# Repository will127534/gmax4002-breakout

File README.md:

# GMAX4002 breakout board
A basic minimum GMAX4002 (1/1.7" 2048x1200 Global shutter) breakout board for Raspberry Pi

In general this is a simple breakout board for GMAX4002 sensor, see [here](https://github.com/will127534/gmax4002-v4l2-driver) on the driver side of things.
The caveat is that you will need to supply trigger pulses to the TEXP test point in order to trigger a new frame from the sensor and the board will not generate that signal for you, as such this is not really a complete board in my opinion but it might be easier for those who are taking this to integrate in their project.  

See the action in video here: [Youtube](https://youtu.be/cdhxaaCYhbM).  
Note that the decoupling capacitor requirements from the leaked pre-released datasheet is a bit... over spec in my opinion(There is no F-way you need 2 x 22uF, 10uF and 100nF for each pixel voltage regulator), the board is deisgned following the datasheet but you can see in the board photos I've omitted some of the capacitors when soldering and it work just fine (I guess).  

At the very least this board has been tested on RPI5 with analog discovery 2 as pulse generating source. Currently I have no plan to continuing develop this board as a raspberry pi camera module but it might be useful for someone looking at this sensor also. Lastly, this project is released as MIT license, do what ever you want with that.

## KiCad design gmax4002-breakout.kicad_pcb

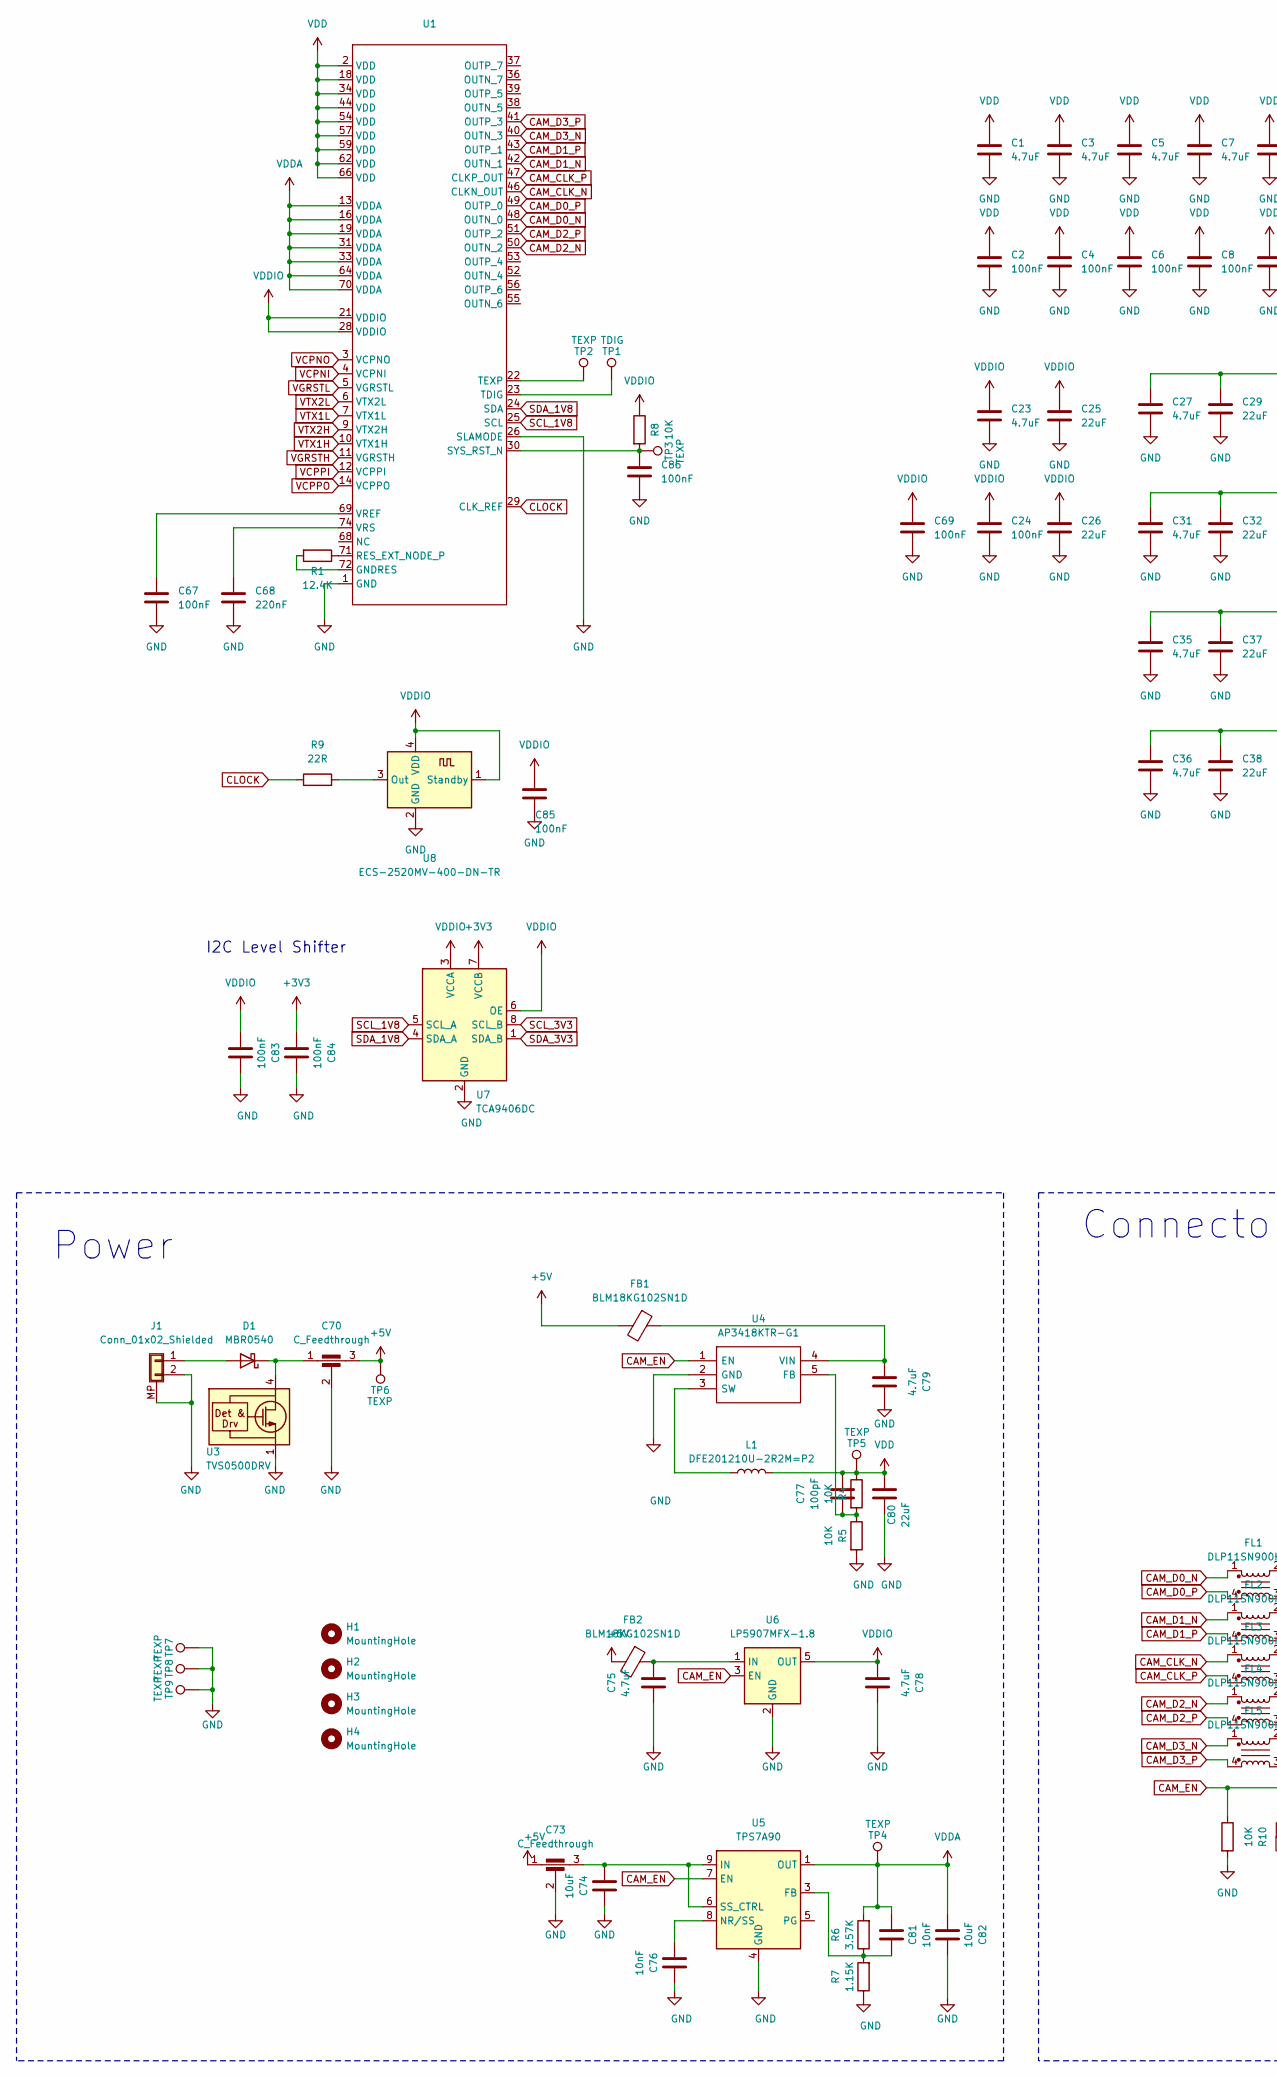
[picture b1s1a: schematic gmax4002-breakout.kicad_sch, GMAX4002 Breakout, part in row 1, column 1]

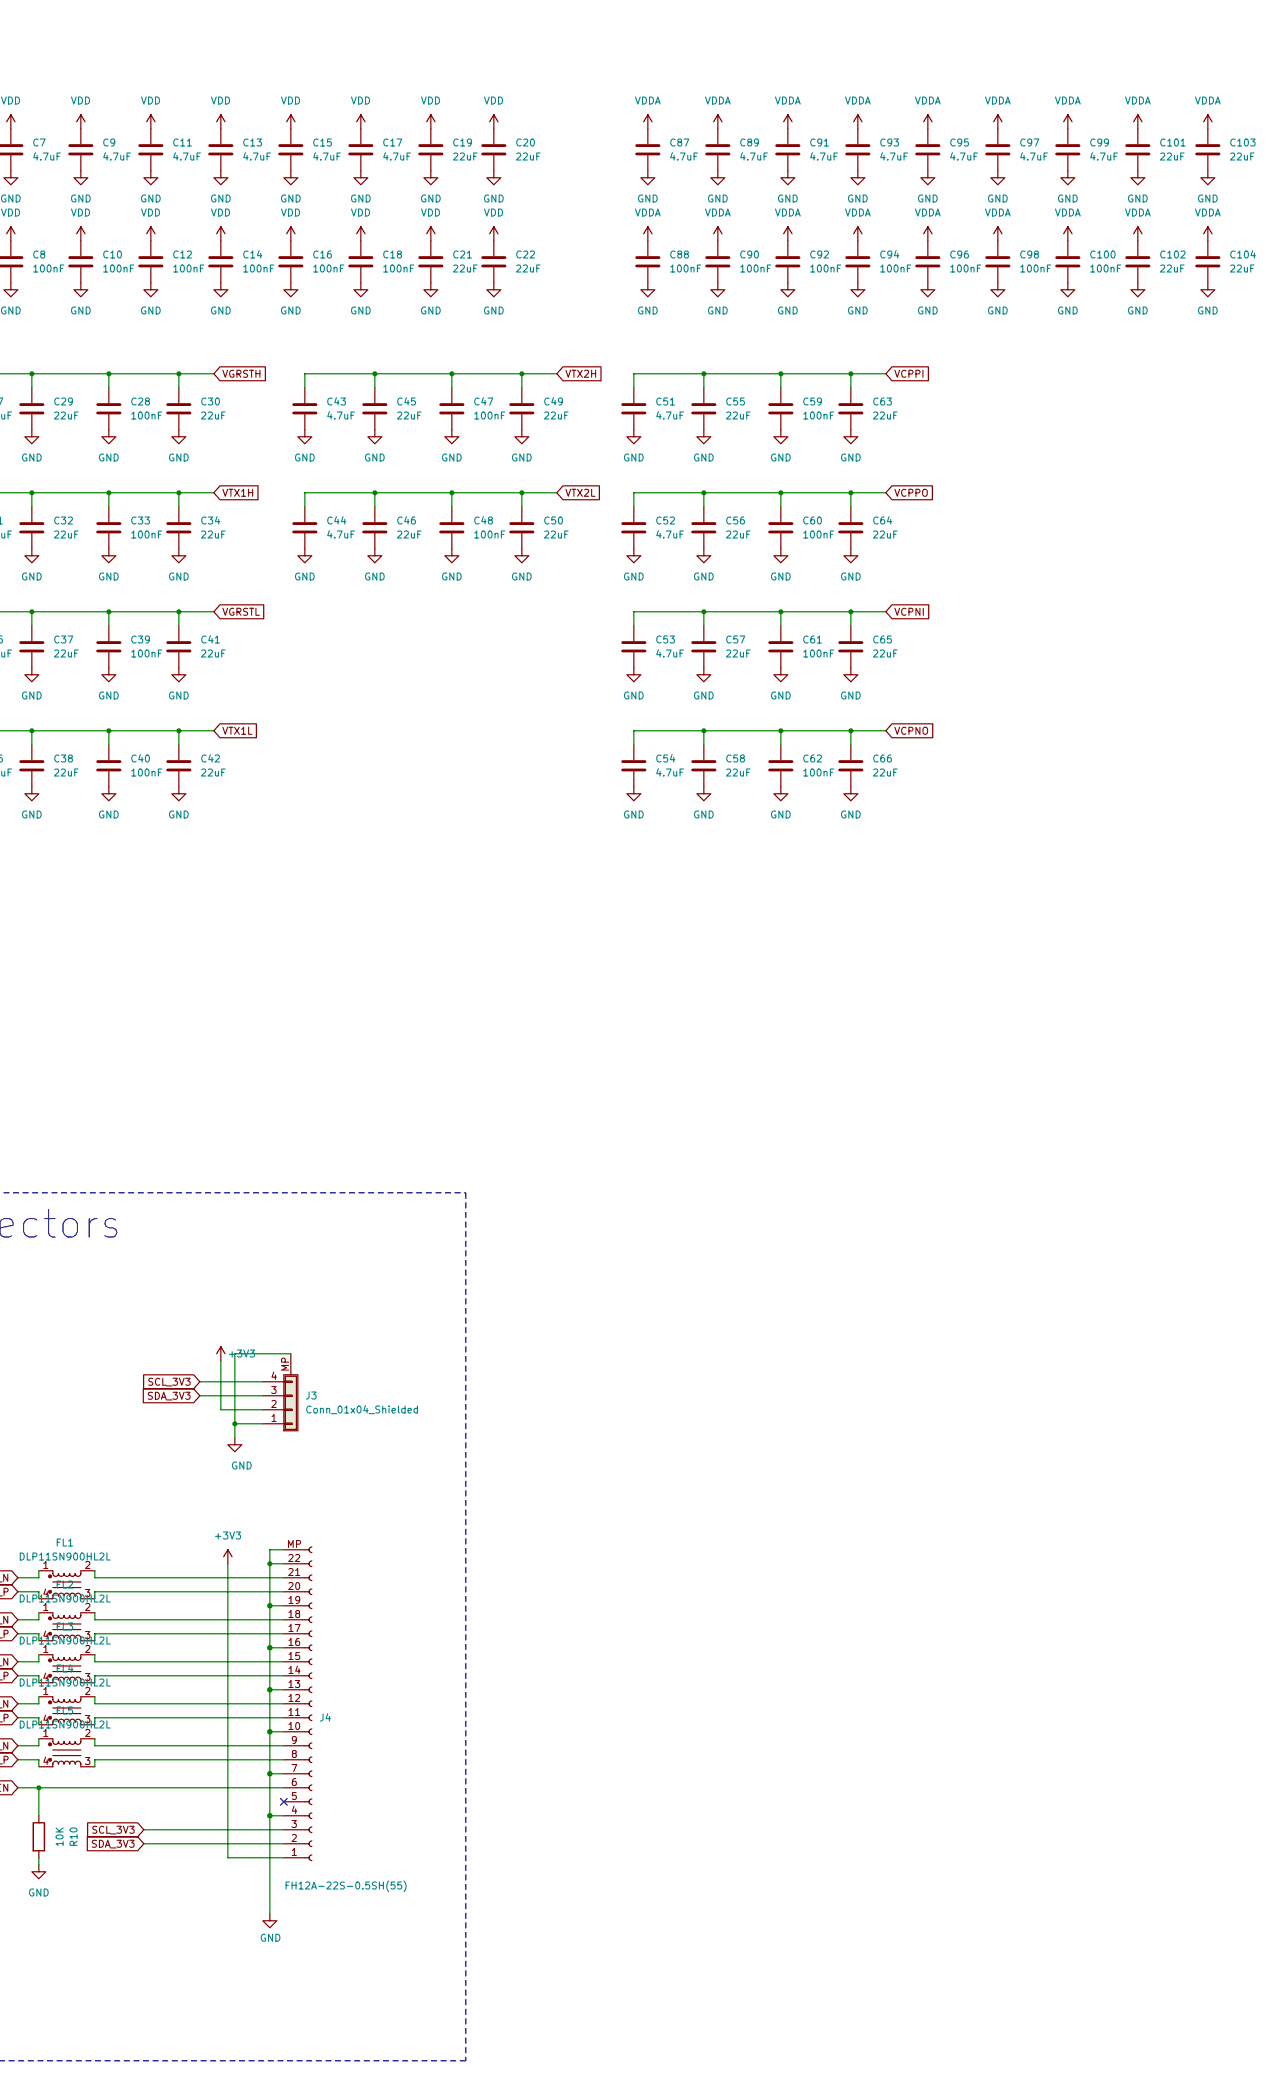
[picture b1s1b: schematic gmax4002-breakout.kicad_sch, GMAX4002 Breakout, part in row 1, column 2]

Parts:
C1, C3, C5, C7, C9, C11, C13, C15, C17, C23, C27, C31, C35, C36, C43, C44, C51, C52, C53, C54, C87, C89, C91, C93, C95, C97, C99: 4.7uF; C_0402_1005Metric
C2, C4, C6, C8, C10, C12, C14, C16, C18, C24, C28, C33, C39, C40, C47, C48, C59, C60, C61, C62, C67, C69, C83, C84, C85, C86, C88, C90, C92, C94, C96, C98, C100: 100nF; C_0402_1005Metric
C19, C20, C21, C22, C25, C26, C101, C102, C103, C104: 22uF; C_0805_2012Metric
C29, C30, C32, C34, C37, C38, C41, C42, C45, C46, C49, C50, C55, C56, C57, C58, C63, C64, C65, C66: 22uF; C_0402_1005Metric
C68: 220nF; C_0402_1005Metric
C70, C73: C_Feedthrough; NFM18CC101R1C3D
C74, C82: 10uF; C_0603_1608Metric
C75, C78, C79: 4.7uF; C_0603_1608Metric
C76, C81: 10nF; C_0402_1005Metric
C77: 100pF; C_0402_1005Metric
C80: 22uF; C_0603_1608Metric
D1: MBR0540; D_SOD-123
FB1, FB2: BLM18KG102SN1D; L_0603_1608Metric
FL1, FL2, FL3, FL4, FL5: DLP11SN900HL2L; DLP11SA350HL2B
H1, H2, H3, H4: MountingHole; MountingHole_2.2mm_M2
J1: Conn_01x02_Shielded; Molex_PicoBlade_53261-0271_1x02-1MP_P1.25mm_Horizontal
J3: Conn_01x04_Shielded; JST_SH_SM04B-SRSS-TB_1x04-1MP_P1.00mm_Horizontal
J4: FH12A-22S-0.5SH(55); Hirose_FH12-22S-0.5SH_1x22-1MP_P0.50mm_Horizontal; Part Description 22 Position FFC, FPC Connector Contacts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
L1: DFE201210U-2R2M=P2; L_0805_2012Metric
R1: 12.4K; R_0402_1005Metric
R4, R5, R8, R10: 10K; R_0402_1005Metric
R6: 3.57K; R_0402_1005Metric
R7: 1.15K; R_0402_1005Metric
R9: 22R; R_0402_1005Metric
TP1: TDIG; TestPoint_Pad_D1.0mm
TP2, TP3, TP4, TP5, TP6, TP7, TP8, TP9: TEXP; TestPoint_Pad_D1.0mm
U1: QFN-74_16.6x12.9_Pitch0.7mm
U3: TVS0500DRV; WSON-6-1EP_2x2mm_P0.65mm_EP1x1.6mm
U4: AP3418KTR-G1; SOT-23-5; Mouser Part Number 621-AP3418KTR-G1
U5: TPS7A90; Texas_S-PDSO-N10_EP1.2x2mm
U6: LP5907MFX-1.8; SOT-23-5
U7: TCA9406DC; TCA9406DCUR
U8: ECS-2520MV-400-DN-TR; Oscillator_SMD_Abracon_ASDMB-4Pin_2.5x2.0mm

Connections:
+3V3: C84.1, J3.2, J4.1, U7.7 (VCCB)
+5V: C70.3, C73.1, FB1.2, FB2.2, TP6.1
CAM_CLK_N: FL3.1, U1.46 (CLKN_OUT)
CAM_CLK_P: FL3.4, U1.47 (CLKP_OUT)
CAM_D0_N: FL1.1, U1.48 (OUTN_0)
CAM_D0_P: FL1.4, U1.49 (OUTP_0)
CAM_D1_N: FL2.1, U1.42 (OUTN_1)
CAM_D1_P: FL2.4, U1.43 (OUTP_1)
CAM_D2_N: FL4.1, U1.50 (OUTN_2)
CAM_D2_P: FL4.4, U1.51 (OUTP_2)
CAM_D3_N: FL5.1, U1.40 (OUTN_3)
CAM_D3_P: FL5.4, U1.41 (OUTP_3)
CAM_EN: J4.6, R10.1, U4.1 (EN), U5.7 (EN), U6.3 (EN)
CLOCK: R9.1, U1.29 (CLK_REF)
GND: C1.2, C2.2, C3.2, C4.2, C5.2, C6.2, C7.2, C8.2, C9.2, C10.2, C11.2, C12.2, C13.2, C14.2, C15.2, C16.2, C17.2, C18.2, C19.2, C20.2, C21.2, C22.2, C23.2, C24.2, C25.2, C26.2, C27.2, C28.2, C29.2, C30.2, C31.2, C32.2, C33.2, C34.2, C35.2, C36.2, C37.2, C38.2, C39.2, C40.2, C41.2, C42.2, C43.2, C44.2, C45.2, C46.2, C47.2, C48.2, C49.2, C50.2, C51.2, C52.2, C53.2, C54.2, C55.2, C56.2, C57.2, C58.2, C59.2, C60.2, C61.2, C62.2, C63.2, C64.2, C65.2, C66.2, C67.2, C68.2, C69.2, C70.2, C73.2, C74.2, C75.1, C76.2, C78.2, C79.2, C80.1, C82.2, C83.2, C84.2, C85.2, C86.2, C87.2, C88.2, C89.2, C90.2, C91.2, C92.2, C93.2, C94.2, C95.2, C96.2, C97.2, C98.2, C99.2, C100.2, C101.2, C102.2, C103.2, C104.2, J1.2, J1.MP (Shield), J3.1, J3.MP (Shield), J4.4, J4.7, J4.10, J4.13, J4.16, J4.19, J4.22, J4.MP, R5.2, R7.1, R10.2, TP7.1, TP8.1, TP9.1, U1.1 (GND), U1.8 (GNDA), U1.15 (GNDA), U1.17 (GND), U1.20 (GND), U1.26 (SLAMODE), U1.27 (GNDA), U1.32 (GNDA), U1.35 (GND), U1.45 (GND), U1.58 (GND), U1.60 (GND), U1.61 (GNDA), U1.63 (GND), U1.65 (GNDA), U1.67 (GND), U1.73 (GNDA), U3.1 (GND), U3.2 (GND), U3.3 (GND), U3.7 (GND), U4.2 (GND), U5.4 (GND), U5.11 (GND), U6.2 (GND), U7.2 (GND), U8.2 (GND)
unnamed: D1.2 (A), J1.1
unnamed: C70.1, D1.1 (K), U3.4 (IN), U3.5 (IN), U3.6 (IN)
unnamed: FL5.3, J4.8
unnamed: FL5.2, J4.9
unnamed: FL4.3, J4.11
unnamed: FL4.2, J4.12
unnamed: FL3.3, J4.14
unnamed: FL3.2, J4.15
unnamed: FL2.3, J4.17
unnamed: FL2.2, J4.18
unnamed: FL1.3, J4.20
unnamed: FL1.2, J4.21
unnamed: R1.2, U1.72 (GNDRES)
unnamed: R1.1, U1.71 (RES_EXT_NODE_P)
unnamed: C86.1, R8.2, TP3.1, U1.30 (SYS_RST_N)
unnamed: TP1.1, U1.23 (TDIG)
unnamed: TP2.1, U1.22 (TEXP)
unnamed: C67.1, U1.69 (VREF)
unnamed: C68.1, U1.74 (VRS)
unnamed: C77.1, R4.2, R5.1, U4.5 (FB)
unnamed: L1.1, U4.3 (SW)
unnamed: C79.1, FB1.1, U4.4 (VIN)
unnamed: C81.1, R6.1, R7.2, U5.3 (FB)
unnamed: C76.1, U5.8 (NR/SS)
unnamed: C73.3, C74.1, U5.6 (SS_CTRL), U5.9 (IN), U5.10 (IN)
unnamed: C75.2, FB2.1, U6.1 (IN)
unnamed: R9.2, U8.3 (Out)
SCL_1V8: U1.25 (SCL), U7.5 (SCL_A)
SCL_3V3: J3.4, J4.3, U7.8 (SCL_B)
SDA_1V8: U1.24 (SDA), U7.4 (SDA_A)
SDA_3V3: J3.3, J4.2, U7.1 (SDA_B)
VCPNI: C53.1, C57.1, C61.1, C65.1, U1.4 (VCPNI)
VCPNO: C54.1, C58.1, C62.1, C66.1, U1.3 (VCPNO)
VCPPI: C51.1, C55.1, C59.1, C63.1, U1.12 (VCPPI)
VCPPO: C52.1, C56.1, C60.1, C64.1, U1.14 (VCPPO)
VDD: C1.1, C2.1, C3.1, C4.1, C5.1, C6.1, C7.1, C8.1, C9.1, C10.1, C11.1, C12.1, C13.1, C14.1, C15.1, C16.1, C17.1, C18.1, C19.1, C20.1, C21.1, C22.1, C77.2, C80.2, L1.2, R4.1, TP5.1, U1.2 (VDD), U1.18 (VDD), U1.34 (VDD), U1.44 (VDD), U1.54 (VDD), U1.57 (VDD), U1.59 (VDD), U1.62 (VDD), U1.66 (VDD)
VDDA: C81.2, C82.1, C87.1, C88.1, C89.1, C90.1, C91.1, C92.1, C93.1, C94.1, C95.1, C96.1, C97.1, C98.1, C99.1, C100.1, C101.1, C102.1, C103.1, C104.1, R6.2, TP4.1, U1.13 (VDDA), U1.16 (VDDA), U1.19 (VDDA), U1.31 (VDDA), U1.33 (VDDA), U1.64 (VDDA), U1.70 (VDDA), U5.1 (OUT), U5.2 (OUT)
VDDIO: C23.1, C24.1, C25.1, C26.1, C69.1, C78.1, C83.1, C85.1, R8.1, U1.21 (VDDIO), U1.28 (VDDIO), U6.5 (OUT), U7.3 (VCCA), U7.6 (OE), U8.1 (Standby), U8.4 (VDD)
VGRSTH: C27.1, C28.1, C29.1, C30.1, U1.11 (VGRSTH)
VGRSTL: C35.1, C37.1, C39.1, C41.1, U1.5 (VGRSTL)
VTX1H: C31.1, C32.1, C33.1, C34.1, U1.10 (VTX1H)
VTX1L: C36.1, C38.1, C40.1, C42.1, U1.7 (VTX1L)
VTX2H: C43.1, C45.1, C47.1, C49.1, U1.9 (VTX2H)
VTX2L: C44.1, C46.1, C48.1, C50.1, U1.6 (VTX2L)

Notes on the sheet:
Connectors
Power
I2C Level Shifter

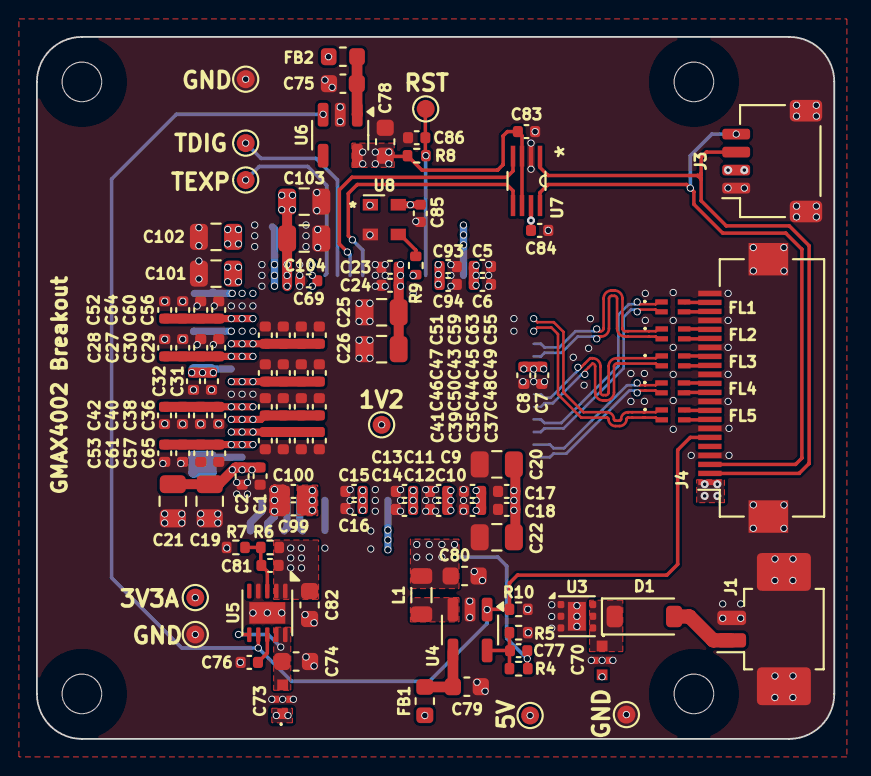
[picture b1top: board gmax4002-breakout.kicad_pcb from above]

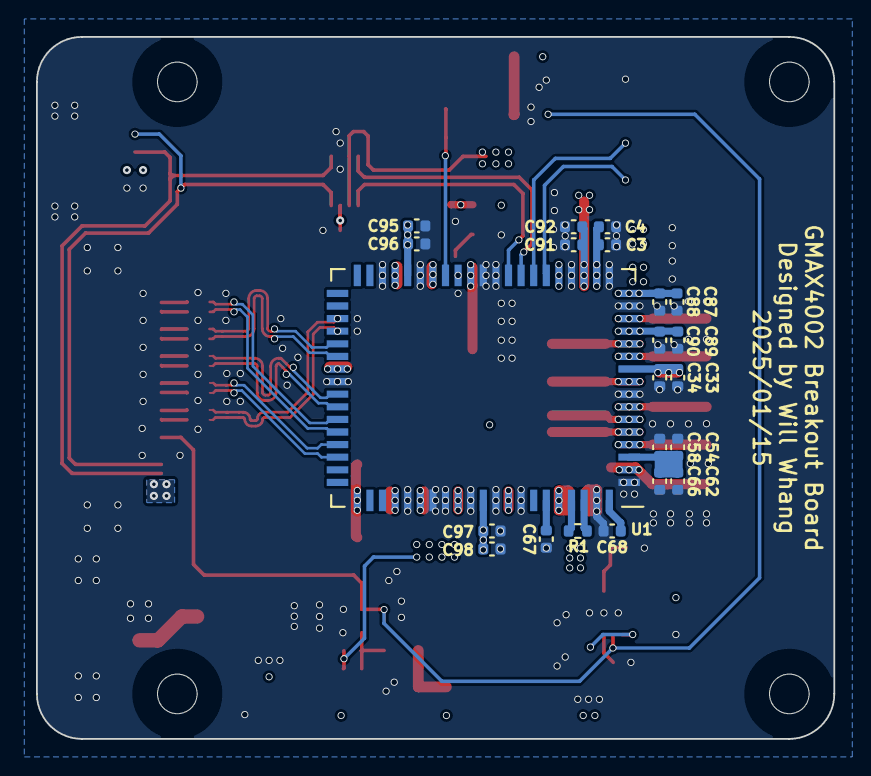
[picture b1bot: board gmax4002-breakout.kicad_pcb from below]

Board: 4 copper layers, 44.3 x 39.0 mm, 142 parts (22 on the bottom side), 59 nets.

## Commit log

2025-09-18 Init basic board files
